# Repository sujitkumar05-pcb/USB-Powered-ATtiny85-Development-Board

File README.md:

# USB-Powered-ATtiny85-Development-Board

## 1. Project Overview

The USB-Powered ATtiny85 Development Board is a compact and low-cost microcontroller development platform designed for quick prototyping and learning purposes. It is based on the ATtiny85, an 8-bit AVR microcontroller, and can be powered directly through a USB interface, eliminating the need for an external power supply.

This board is intended to simplify development by providing easy access to essential pins, stable power regulation, and support for programming via commonly used USB-based programmers. Its small form factor makes it ideal for embedded applications, wearable electronics, and space-constrained projects.

The project focuses on:

Minimal component count for reliability and ease of assembly

USB power convenience for plug-and-play operation

Compatibility with Arduino-based workflows and AVR toolchains

Educational and hobbyist-friendly design

This development board is suitable for beginners learning microcontroller basics as well as engineers needing a simple ATtiny85-based solution for rapid prototyping.

## 2. Key Learning Objectives

Understand ATtiny85 microcontroller basics

Learn USB-powered circuit design

Practice schematic and PCB layout design

Gain experience in programming and testing AVR microcontrollers
-----

## 3. Tools & Software Used
- **KiCad EDA**
  - Schematic Editor  
  - PCB Layout Editor  
  - 3D Viewer
 
 ---

## 4. Project Files
- Schematic design files (`.kicad_sch`)  
- PCB layout files (`.kicad_pcb`)  
- 3D render images  
- Manufacturing-ready Gerber files  

---

## 5. Block-Level Working Explanation

The USB port supplies 5 V power to the board, which powers the ATtiny85 microcontroller. The microcontroller executes the programmed logic and controls the I/O pins. External components or modules connected to these pins interact with the ATtiny85 for input and output operations.
## 6. Bill of Materials (BOM)
| S. No. | Reference | Value          | Footprint                                             | Qty |
| -----: | --------- | -------------- | ----------------------------------------------------- | --: |
|      1 | C1        | 1 µF           | Capacitor_SMD:C_1210_3225Metric                       |   1 |
|      2 | C2        | 4.7 µF         | Capacitor_SMD:C_1210_3225Metric                       |   1 |
|      3 | C3        | 0.1 µF         | Capacitor_SMD:C_1210_3225Metric                       |   1 |
|      4 | D1        | 1N5819         | Diode_THT:D_DO-41_SOD81_P10.16mm_Horizontal           |   1 |
|      5 | D2, D3    | BZT52C36       | Diode_SMD:D_SOD-123F                                  |   2 |
|      6 | D4, D5    | LED            | LED_SMD:LED_1210_3225Metric                           |   2 |
|      7 | J1        | Conn_01x03_Pin | Connector:FanPinHeader_1x03_P2.54mm_Vertical          |   1 |
|      8 | J2        | USB Micro      | Connector_USB:USB_A_CNCTech_1001-011-01101_Horizontal |   1 |
|      9 | J3        | Conn_01x06_Pin | Connector_JST:JST_PH_B6B-PH-K_1x06_P2.00mm_Vertical   |   1 |
|     10 | R1        | 1 kΩ           | Resistor_SMD:R_1210_3225Metric                        |   1 |
|     11 | R2, R3    | 66.5 Ω         | Resistor_SMD:R_1218_3246Metric                        |   2 |
|     12 | R4, R5    | 1 kΩ           | Resistor_SMD:R_1218_3246Metric                        |   2 |
|     13 | U1        | L78L05         | Package_SO:SOIC-8_3.9×4.9 mm_P1.27 mm                 |   1 |
|     14 | U2        | ATtiny85-20S   | Package_SO:SOIC-8_5.3×5.3 mm_P1.27 mm                 |   1 |

## 7. Images & Renders

- **Schematic**

- **PCB Layout**

 - **3D View**

---

## 8. Disclaimer
This project is developed for educational and learning purposes only. The design has been tested to the best of the author’s knowledge; however, no guarantee is provided regarding performance or suitability for commercial or safety-critical applications. Use the design at your own risk.
Users are advised to follow proper electrical safety standards, use appropriate protective components, and verify the design thoroughly before real-world deployment

---

## 9. Author
- **Name:** SUJIT KUMAR
- **Toolchain:** KiCad EDA  

ato z
#

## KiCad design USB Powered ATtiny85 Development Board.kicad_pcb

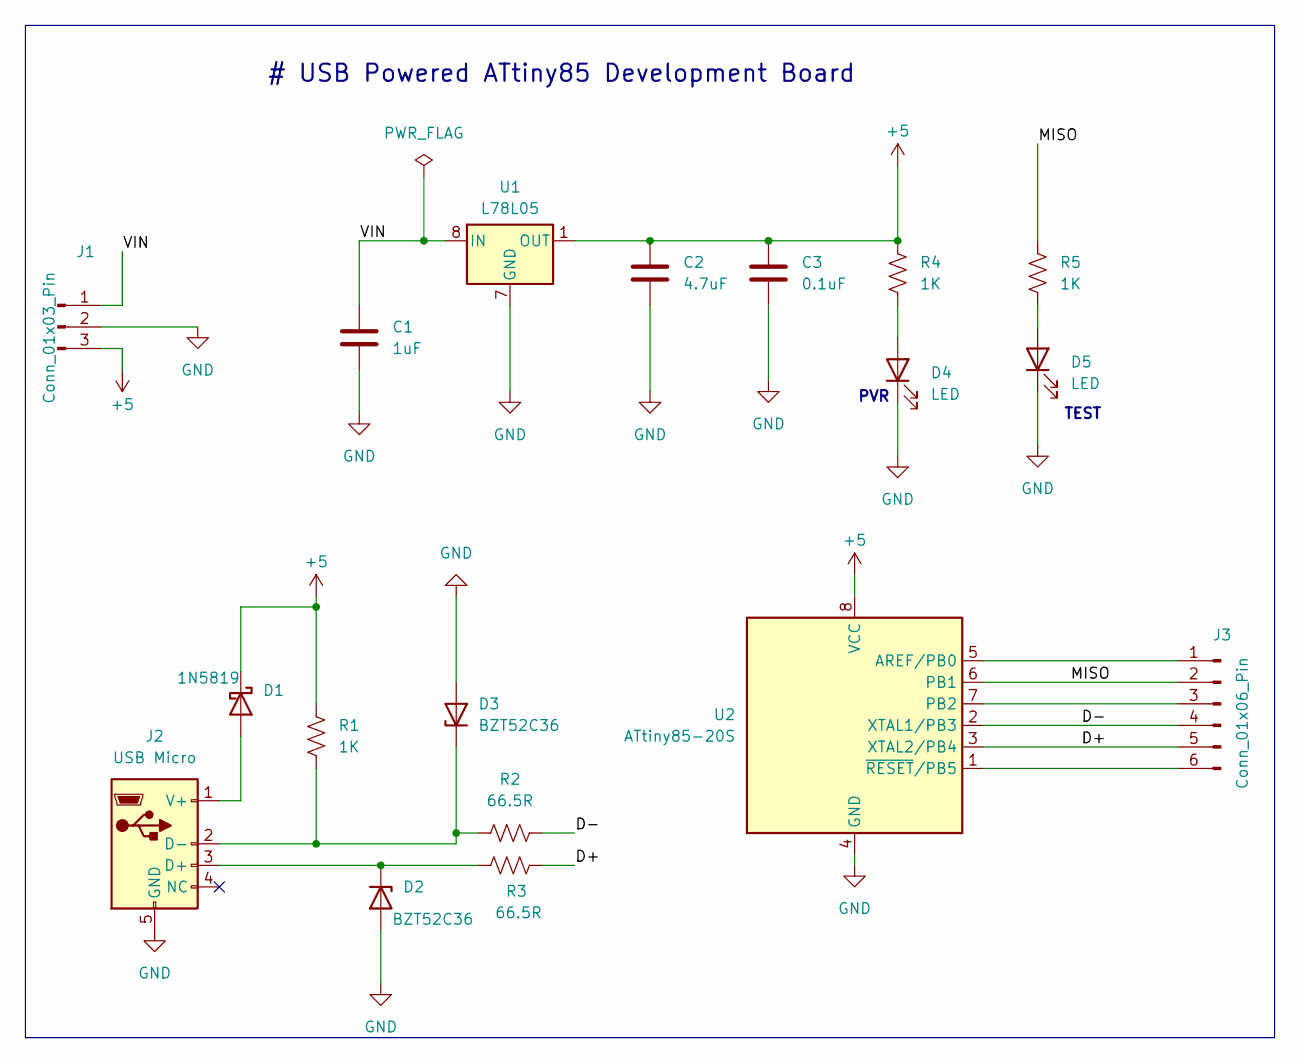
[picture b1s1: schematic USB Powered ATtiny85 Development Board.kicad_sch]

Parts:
C1: 1uF; C_1210_3225Metric
C2: 4.7uF; C_1210_3225Metric
C3: 0.1uF; C_1210_3225Metric
D1: 1N5819; D_DO-41_SOD81_P10.16mm_Horizontal
D2, D3: BZT52C36; D_SOD-123F
D4, D5: LED; LED_1210_3225Metric
J1: Conn_01x03_Pin; FanPinHeader_1x03_P2.54mm_Vertical
J2: USB Micro; USB_A_CNCTech_1001-011-01101_Horizontal
J3: Conn_01x06_Pin; JST_PH_B6B-PH-K_1x06_P2.00mm_Vertical
R1: 1K; R_1210_3225Metric
R2, R3: 66.5R; R_1218_3246Metric
R4, R5: 1K; R_1218_3246Metric
U1: L78L05; SOIC-8_3.9x4.9mm_P1.27mm
U2: ATtiny85-20S; SOIC-8_5.3x5.3mm_P1.27mm

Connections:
+5: C2.1, C3.1, D1.1 (K), J1.3, R1.2, R4.1, U1.1 (OUT), U2.8 (VCC)
/D+: J3.5, R3.2, U2.3 (XTAL2/PB4)
/D-: J3.4, R2.2, U2.2 (XTAL1/PB3)
/MISO: J3.2, R5.1, U2.6 (PB1)
/VIN: C1.1, J1.1, U1.8 (IN)
GND: C1.2, C2.2, C3.2, D2.2 (A), D3.2 (A), D4.1 (K), D5.1 (K), J1.2, J2.5 (GND), U1.2 (GND), U1.3 (GND), U1.6 (GND), U1.7 (GND), U2.4 (GND)
unnamed: D1.2 (A), J2.1 (V+)
unnamed: D2.1 (K), J2.3 (D+), R3.1
unnamed: D3.1 (K), J2.2 (D-), R1.1, R2.1
unnamed: D4.2 (A), R4.2
unnamed: D5.2 (A), R5.2
unnamed: J3.1, U2.5 (AREF/PB0)
unnamed: J3.3, U2.7 (PB2)
unnamed: J3.6, U2.1 (~RESET/PB5)

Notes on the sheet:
TEST
# USB Powered ATtiny85 Development Board
PVR

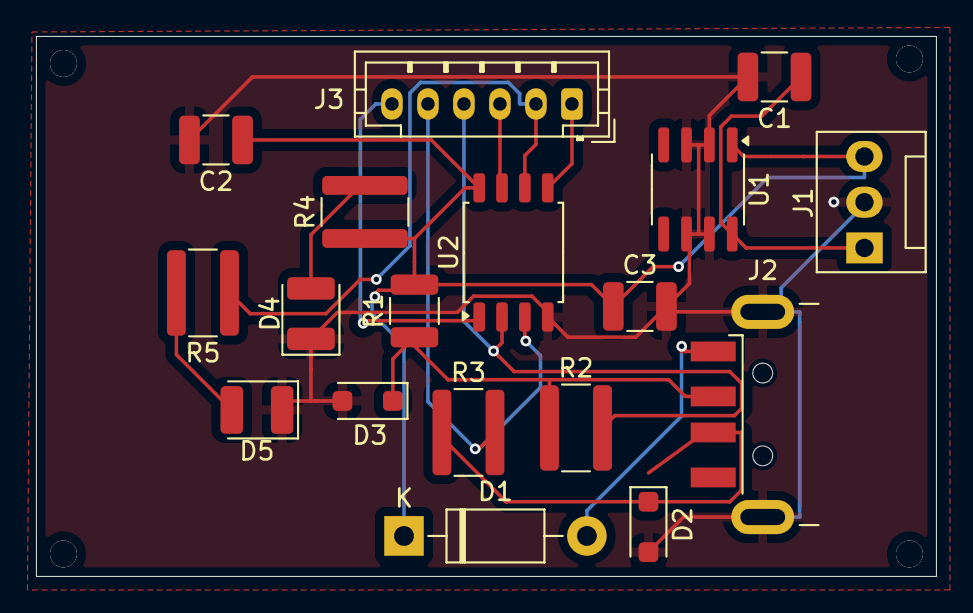
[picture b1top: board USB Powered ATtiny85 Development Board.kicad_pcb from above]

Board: 2 copper layers, 50.0 x 30.0 mm, 18 parts (0 on the bottom side), 14 nets.
